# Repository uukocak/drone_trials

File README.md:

# Unnamed Drone Project

Openpilot inspired personal drone project. It is a hobby project with no future expectations.

## Current Progress

### Board Design
  - Design made using OpenPilot CC3D board schematic with little component changes.
  - First prototype builted and will be tested.
### Mechanical Design
  - A small drone body sketched and designed on Solidworks 
  - Mechanical prototype 3D printed.
### Software Development
  - Pending...

Check the orginal OpenPilot project at  :
- https://github.com/librepilot
- https://opwiki.readthedocs.io/en/latest/index.html

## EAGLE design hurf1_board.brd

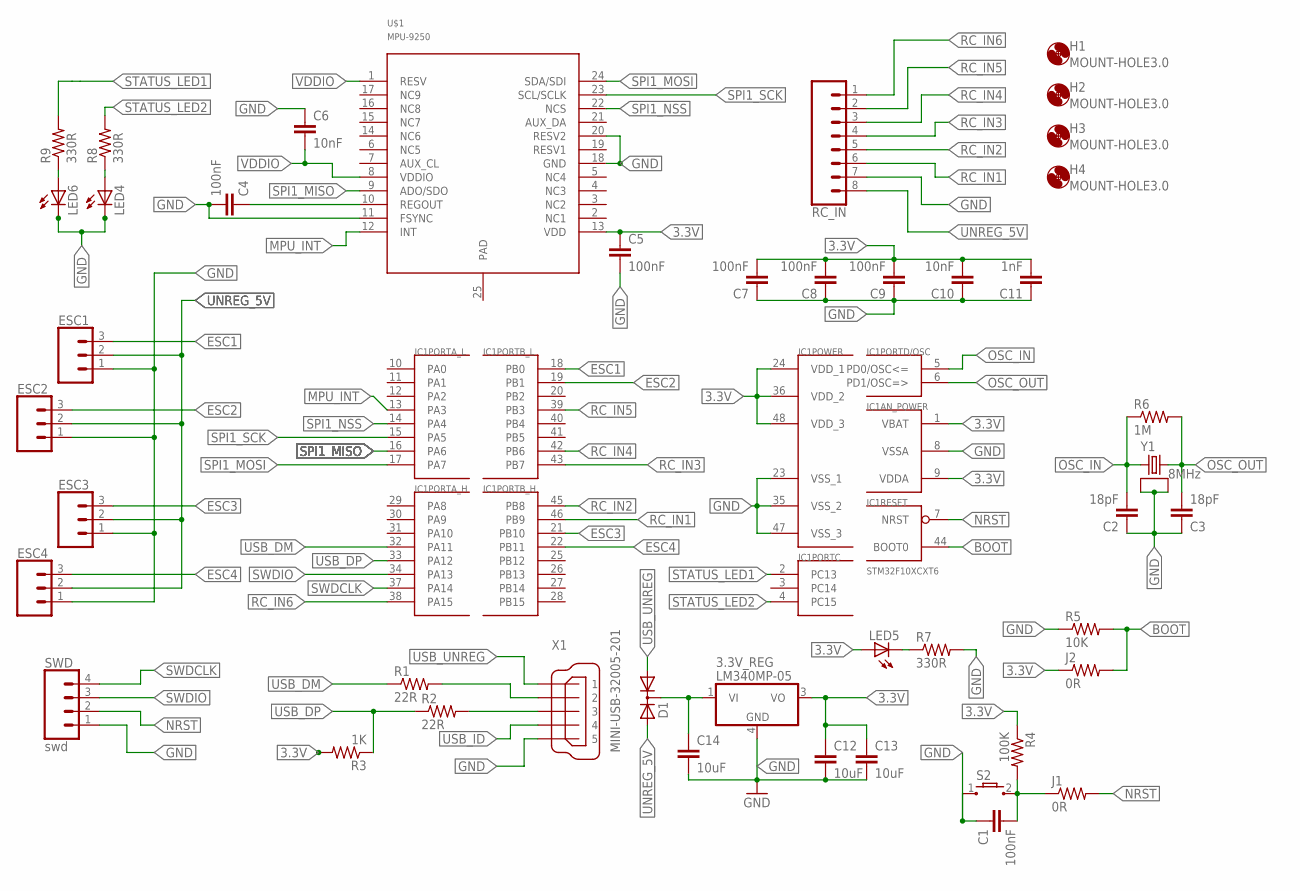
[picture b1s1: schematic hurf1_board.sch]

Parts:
3.3V_REG: LM340MP-05; SOT223
C1, C5, C7, C8, C9: 100nF; C0603
C2, C3: 18pF; C0603
C4: 100nF; C0805K
C6, C10: 10nF; C0603
C11: 1nF; C0603
C12, C13, C14: 10uF; C0805
D1: SOT23
ESC1, ESC2, ESC3, ESC4: CONN_03; 1X03
H1, H2, H3, H4: MOUNT-HOLE3.0; 3,0
IC1: STM32F10XCXT6; TQFP48
J1, J2: 0R; R0603
LED4, LED5, LED6: LEDSML0805; SML0805
R1, R2: 22R; R0603
R3: 1K; R0603
R4: 100K; R0603
R5: 10K; R0603
R6: 1M; R0603
R7, R8, R9: 330R; R0603
RC_IN: CONN_08; 1X08_1MM_RA
S2: TL3302_GULL_WING
SWD: swd; 1X04_1MM_RA
U$1: MPU-9250; LEAD-QFN24
X1: MINI-USB-32005-201; 32005-201
Y1: 8MHz; GSX-531

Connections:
3.3V: 3.3V_REG.3 (VO), C5.1, C7.2, C8.2, C9.2, C10.2, C11.2, C12.1, C13.1, IC1.1 (VBAT), IC1.9 (VDDA), IC1.24 (VDD_1), IC1.36 (VDD_2), IC1.48 (VDD_3), J2.1, LED5.A, R3.2, R4.1, U$1.13 (VDD)
BOOT: IC1.44 (BOOT0), J2.2, R5.2
ESC1: ESC1.3, IC1.18 (PB0)
ESC2: ESC2.3, IC1.19 (PB1)
ESC3: ESC3.3, IC1.21 (PB10)
ESC4: ESC4.3, IC1.22 (PB11)
GND: 3.3V_REG.4 (GND), C1.1, C2.1, C3.1, C4.2, C5.2, C6.1, C7.1, C8.1, C9.1, C10.1, C11.1, C12.2, C13.2, C14.2, ESC1.1, ESC2.1, ESC3.1, ESC4.1, IC1.8 (VSSA), IC1.23 (VSS_1), IC1.35 (VSS_2), IC1.47 (VSS_3), LED4.C, LED6.C, R5.1, R7.2, RC_IN.7, S2.1, SWD.1, U$1.11 (FSYNC), U$1.18 (GND), U$1.20 (RESV2), X1.5, Y1.2, Y1.4
MPU_INT: IC1.13 (PA3), U$1.12 (INT)
unnamed: R1.2, X1.2
unnamed: R2.2, X1.3
unnamed: C4.1, U$1.10 (REGOUT)
unnamed: 3.3V_REG.1 (VI), C14.1, D1.3 (C)
unnamed: C1.2, J1.1, R4.2, S2.2
unnamed: LED6.A, R9.1
unnamed: LED5.C, R7.1
unnamed: LED4.A, R8.1
NRST: IC1.7 (NRST), J1.2, SWD.2
OSC_IN: C2.2, IC1.5 (PD0/OSC<=), R6.1, Y1.1
OSC_OUT: C3.2, IC1.6 (PD1/OSC=>), R6.2, Y1.3
RC_IN1: IC1.46 (PB9), RC_IN.6
RC_IN2: IC1.45 (PB8), RC_IN.5
RC_IN3: IC1.43 (PB7), RC_IN.4
RC_IN4: IC1.42 (PB6), RC_IN.3
RC_IN5: IC1.39 (PB3), RC_IN.2
RC_IN6: IC1.38 (PA15), RC_IN.1
SPI1_MISO: IC1.16 (PA6), U$1.9 (ADO/SDO)
SPI1_MOSI: IC1.17 (PA7), U$1.24 (SDA/SDI)
SPI1_NSS: IC1.14 (PA4), U$1.22 (NCS)
SPI1_SCK: IC1.15 (PA5), U$1.23 (SCL/SCLK)
STATUS_LED1: IC1.2 (PC13), R9.2
STATUS_LED2: IC1.4 (PC15), R8.2
SWDCLK: IC1.37 (PA14), SWD.4
SWDIO: IC1.34 (PA13), SWD.3
UNREG_5V: D1.2 (A2), ESC1.2, ESC2.2, ESC3.2, ESC4.2, RC_IN.8
USB_DM: IC1.32 (PA11), R1.1
USB_DP: IC1.33 (PA12), R2.1, R3.1
USB_ID: X1.4
USB_UNREG: D1.1 (A1), X1.1
VDDIO: C6.2, U$1.1 (RESV), U$1.8 (VDDIO)

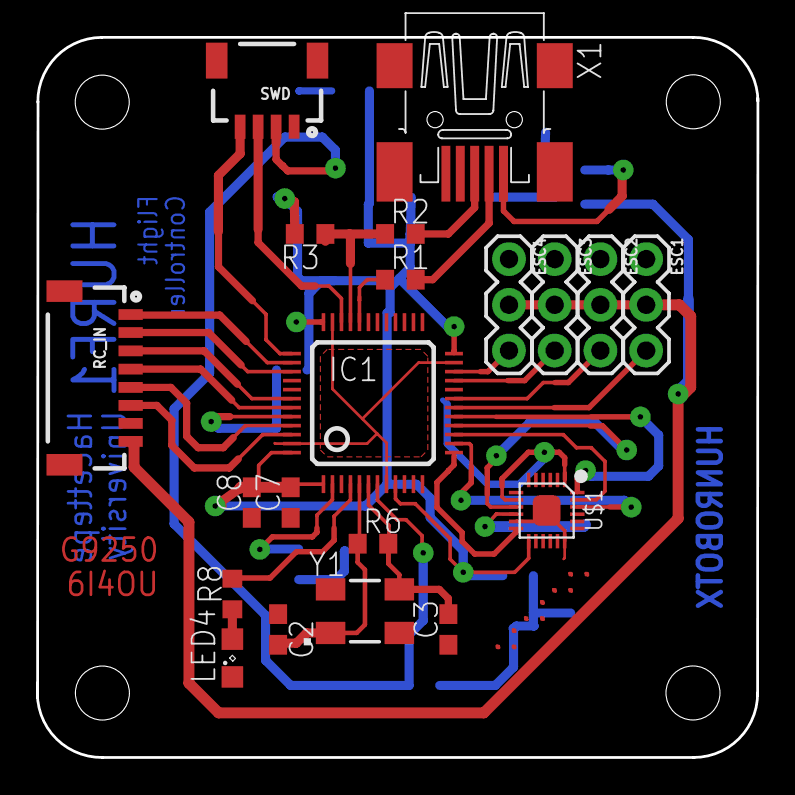
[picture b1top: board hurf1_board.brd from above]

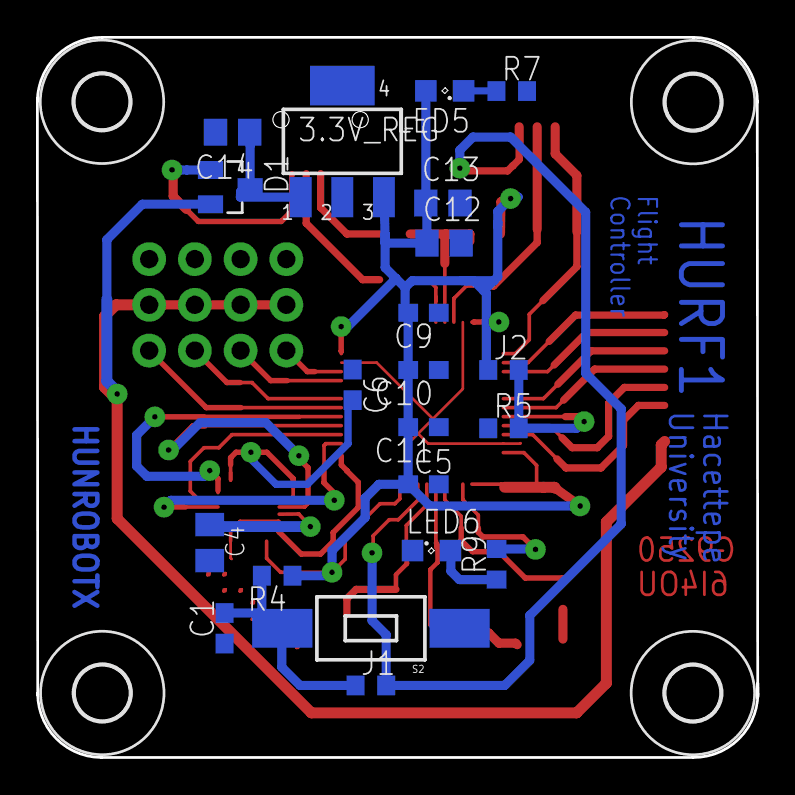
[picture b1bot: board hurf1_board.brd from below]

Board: 2 copper layers, 40.0 x 40.0 mm, 45 parts (25 on the bottom side), 38 nets.

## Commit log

2016-12-18 Git initialized
    :added .gitignore
2016-12-18 Resource Folder Created
    RESOURCE:Added STM32F103C8T6 datasheet
2017-07-05 Initial Commit -schematic added WIP -board added PRE =.gitignore added
2017-07-09 Schematic Completed -schematic w1 -board w1 -controlboard sketch added (.dxf) =.gitignore updated = hurf1_schematic.sch -> hurf1_board.sch = board images added
2017-07-13 Circuit Size Shrinked -schematic w1 (updated) -board w1s1 (updated) *SMD Package changed from 0805 -> 0603 *SWD Port changed from DIL -> JST-SH X UNREG_5V pin must be connected to diode
2017-07-14 Circuit Design Updated -schematic w1(updated) *1x Power Led , 2x Status Led Added *RC_OUT and SWD packages updated -board w1s1 (updated) *All connections solved *Schematic changes applied X* RC_IN po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
2017-07-15 Final touches to board -schematic w1 (updated) *RC_IN port package updated from DIL -> JST-SH -board w1s1(updated) *Schematics changes applied *General check successful *Signs and Logos added -Status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
2017-07-18 Drills added , gerber out -schematic w1 (updated) -board w1s1 (updated) *Corner Mount holes added (3mm) *Board corners rounded *Signs and logos rearrenged -Status : RTF =gerber_out files added
2017-07-23 Set theme jekyll-theme-slate
2017-07-23 Documentation added =Bottom and Top component place scheme added =Schematic exported as png file =add_notes.txt added
2017-08-12 Resource Folder Updated -Dual Diode DS added -MPU9250A DS added -STM32F10xxx Ref. Man. added -SMD Crystal DS added
2018-09-26 Directory Update
2018-09-26 Mechanical Design Files
    - Sample design files for first prototype added
    - Ready to print STL files added
2018-09-26 Mechanical Design Files
    - Sample design files for first prototype added
    - Ready to print STL files added
    - Readme Update
2018-11-28 Experimental PID lib add
    Not tested nor compiled!

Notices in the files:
parts and their libraries:
Golledge: © Golledge Electronics Ltd 2016. Released under GNU General Public License. Full library June 2016.
SparkFun-Connectors: Licensing: Creative Commons ShareAlike 4.0 International - https://creativecommons.org/licenses/by-sa/4.0
